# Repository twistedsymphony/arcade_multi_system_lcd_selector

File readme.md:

# twistedsymphony's universal multi-kit LCD Selector (aka CAERTF-MS)

# F.A.Q.

**What is this thing?**

This is a small remote selector that can be adapted and used on DIP-switch based arcade multi-systems. 
Once the device is configured and installed, rather than selecting your game by setting dip switches, users can push the "Up" (D0) and "Down" (D2) buttons to navigate visually through the game list, then push "Select" (D1) to select the game. The selector will then hold the arcade board in reset and electrically configure the dip switches before releasing reset allowing the selected game to boot.

**What is a DIP-switch based arcade multi-system?**

It's pretty niche, but some arcade games share the same electronics and only really have differing software. Arcade Enthusiests have designed and built "multi-systems" that allow switching out the software so that rather than having a whole separate set of electronics for each game, one set of electronics can play multiple games. The simpliest of these multi-systems will often use Dip-switches to set the game, which is cheap and effective but can be quite clumsy and unintuitive to use.

**Why was this made?**

Selecting your game using dip-switches can be frustrating, annoying, and very much non-intuitive. You typically need to have a little chart near by that tells you how to set the dip switches for the game you want to play, and if you want to switch games you have to power everything down to change it. Doing this while your arcade PCB is inside of an arcade cabinet means you sometimes have to be a contortionist with night-vision and the dexterity of a bomb-diffusal expert just to change that game you're playing. A selector like this one, that is easy to use and understand, solves most of those problems. 

This is being made open source in the hopes that future multi-systems that get developed by anyone in the community can easily incorporate support for this benefiting both the functionality of their multi and the users in the community. 

**What features/functinoality does this have?**

You get a full-color TFT display to show the game logos, you get 3 buttons: up, down, and select, so you can scroll through the game list and select the game you'd like to play. Selecting the game displays a loading screen while it resets the PCB and virtually configures the dip switches for game you selected. If an image isn't found it it will display the title of the game as text on the screen, and can seemilessly scroll between text and image based entries. It uses a standard 10-pin IDC ribon cable connection to the multi so you can remote mount the selector outside the cab by simply buying a cable long enough for your setup.

Through the menu configuration file you can control:
* what image is displayed with each game
* what image to display for the loading screen
* what text is to be displayed if an image isn't available
* what the dip configuration is for each selection
* what order you would like the games to appear in (you can even have the same game appear multiple times, in multiple places or with multiple names or images if you like)
* which games you would like displayed in the list or not displayed in the list
* which game you would like to load by default when you first power on
* the amount of idle time before the menu to goes back to displaying the current running game if you scrolled without selecting anything and then stopped

See the section below on "reconfiguring the menu_config.json file" for details on how to adjust these settings.

future features:
* remember last game. The code has support to remember the last selected game on power down and select that game on next power up, but there's a bug that's preventing that from functioning
* Selection over WiFi from your phone or other devie. the selector has Wifi Support so this is possible, the software just needs to be built.

**How Difficult is this to setup and use?**

If you're designing and building a multi kit this will add exactly $0 to your production costs. For the bare minimum support you simply need to add a 10-pin header footprint to your PCB for the selector and a 1-pin header footprint for a reset wire. This adds no cost to production and maybe an hour (not even) of your time to add the header to your schematic and PCB layout. I've even provided pre-configured footprints to allow mounting of the selector directly to your PCB if you have the room for it. If you want stronger support still you can spend a few extra cents per PCB and solder in the headers to each of the footprints you added to make use of the LCD selector completely plug and play for your users.

If you're a user of multis the difficulty varies depending on the multi-kit, setting up the kit at most would require soldering of some simple through-hole parts. The selector itself uses an off-the-shelf display and MCU unit from Adafruit coupled with a custom designed interface PCB that is open source and you can send the design files out and have made completely, or find someone selling them. Installing the software is as simple as copying files over to a USB thumb drive.

**Can this be used on multi-kits that weren't designed for it?**

Potentially, from an electrical standpoint this can be used with any multikit design to select games by up to 7 dip-switches (or jumpers). The challenge is wiring it up in a way that doesn't look like a science-experiment, which will vary greatly depending on the multi. The software is fully customizable, in addition to the "menu" config file there is a separate "multi" config file that allows you to specify the parameters of the multi for the software to tailor itself for it's use without any code changes.

# Putting Together a Selector as a Multi-Kit User

## Building a Selector
To piece together a selector you need 3 parts:
1. An Adafruit ESP32-S2 Reverse TFT Feather, which can be [purchased directly from Adafruit](https://www.adafruit.com/product/5345)
2. An CAERTF-MS Interface PCB, the schematics footprint, BOM, and ready-to-go production files are available within this repo
3. a 10-pin IDC cable. Multi-kits designed for selector mounting using the footprints in this repo are designed to utilize a 1.5in (38mm) length cable which can be [purchased from Adafruit](https://www.adafruit.com/product/556) though any 10-pin (2x5 female to female) IDC cable should work.

the Adafruit ESP32-S2 Reverse TFT Feather unit includes 2 male pin header rows, you will need to solder these to the unit to allow it to plugin to the CAERTF-MS interface PCB. While looking at the LCD with USB port on the left you will want to solder the entire bottom row of pins and the first 4 pins on the top left to allow it to plug into a CAERTF-MS Interface PCB and complete the assembly. 

## Setting up a Software release on a new Selector.
1. With the selector disconnected from both the multi-kit and the CAERTF-MS interface board, and disconnected from any power source, connect a USB-C cable between the selctor and your PC. 
2. If this is the first time configuring the selector the display on the selector should say "Adafruit Feather" with some information about the button and "battery" voltages, this is just the default software loaded. On the back of the display you should see a green and blue LED and there is a small reset button next to the USB port, you'll want to click this button once to reset, then double click it to put it into bootloader mode. If successful you should see the screen change and your PC should recognize a USB storage device called "FTHRS2BOOT" If not, attempt the reset button sequence again (the timing between the first click to reset and the subsequent double click can be tricky to get right)
3. Copy the latest Circuit Python .UF2 file file to the root of the "FTHRS2BOOT" drive. You can [get this file from the circuitpython website]( https://circuitpython.org/board/adafruit_feather_esp32s2_reverse_tft/) (at the time of this writing 9.2.8 was the lastest version and known to work)
4. Once the file has been copied over, the display should automatically restart and it will display some small white text on the screen and you will now see a new USB storage device attached to your computer called "CIRCUITPY"
5. Copy the entire content of a release file over to the root folder of the CIRCUIT PY drive. your computer will likely ask if you want to overwrite code.py, select yes to overwrite.

Releases should include:
  * code.py from the he /source directory here on github 
  * multi_config.json and menu_config.json configuring the selector specificlly to your multi kit
  * a /lib folder with the adafruit_display_text library
  * a /images fold that includes the loading.bmp image along with .bmp images for each game the multi supports.
4. you can now test out the menu to make sure it has the games you expect and see how it functions before connecting it to your multi. If you'd like to ajust settings in "menu_config.json" file you can do so to configure the menu to your liking and confirm those changes work while you still have it hooked up to your PC. it is NOT recommended to adjust the multi_config.json settings as these determine the electrical configurain for the multi.
5. once you're done simply unplug the USB-C cable from the display and now the software on the selector is ready for the multi.

**NOTE: Do not connect the USB-C on the Selector at the same time the 10-pin connector is attached to the Multi PCB** Doing so risks damaging your USB host device. The interface PCB has some protections to help prevent voltage back-feed from the USB port to the Multi-PCB but there are no protections to stop voltage back feed from the multi-PCB to the USB port as such there is risk of damage to your USB Host device.

## Installing a Selector onto your Multi
1. Follow the steps above to build the selector hardware
2. Follow the steps above to install the software on the selector
3. Ensure that all Dips switches on your multi are set to "OFF" (0) and that any rotary selectors are set to position "0". Alternatively, you can completely remove any dips or rotary switches from your multi-PCB (if you set any of these switches to other positions it causes that dip to perminently register as "on" resuling in different selections being made other than the game you selected on the LCD selector)
3. Plug the Adafruit ESP32-S2 Reverse TFT Feather into the CAERTF-MS Interface PCB, Make sure the USB-C port is disconnected (**Do not connect the USB-C on the Selector at the same time the 10-pin connector is attached to the Multi-PCB** the interface PCB has some protections to help prevent voltage back-feed from the USB port to the Multi-PCB but there are no protections to stop voltage back feed from the multi-PCB to the USB port as such there is risk of damage to your USB Host device.)
4. Connect the 10-pin IDC cable between the selector and the appropriate header on your multi-PCB
5. (optional) Install any mounts or brackets that may be avalable for your particular multi

## Making Images for the Selector
Images for the selector should be 240x135 pixels and .bmp format. it's recommended to used 8-bit indexed color format for the .bmp as this should set the file size to 33kb for each image. This is small enough to support 32 images for multis with 5-dip switches (32 game slots) or less. For multis with 6 dips (64 game slots) or 7 dips (128 game slots) you will likely need to get creative with lower bit-depth color or use text rather than images for some games.

While BMP files are larger the processing speed required to decode .jpg or .png compression on images takes about 1-2 seconds per image load which dramatically slows down menu navigation making the game selection experience feel extremely laggy. BMP was chosen as it is essentially uncompressed and is able to load instantly and at 8-bit indexed color is still small enough to support images for all games on nearly all dip-switch based multis.

## reconfiguring the menu_config.json file
The Configuration files on this multi are stored in a json format. You can use any plain text editor (such as notepad) to edit a .json file. If the formatting is incorrect or if any value is set incorrectly the multi will display an error on the screen explaining the issue rather than booting to the menu. It's highly recommeded that you use an existing working menu_config.json file and modify when developing a configuration file for a new multi, or adjusting your preferences for an existing multi. this will help you understand the format and parameters.

"games" are identified with a text string, I use the mame rom name for simplicity and consistency but any string of text can be used so long as it's used consistently through the config file. image file paths are always from the root of the device, and by default will use the "/image/filename.bmp" path and format.

There are three sections to the menu_config.json file, the main configuration which describes how the menu functions, the "game_order" list which simply describe the order that the games will apepar in the menu, and the "gamedefs" list which describes each game, it's title, which image it uses, and it's hex value in dips or on a rotary selector.

The main config has the following value and parameter pairs:
* multi_name: [string] This is simply a string of text to help identify which multi the menu is for, it's not used by the multi at all and really just useful to human readers of the config file.
* default_game: [string] this is the game that will start by default when the multi is powered on, it must be set to a value that matches a game identifier in the gamedefs section. if you do not have a preference it is recommended to set this to which ever game occupies position 0 (all dips off) as that will allow initial board bring up about 2 seconds faster.
* retain_selection: [boolean] this is a true or false value, when true the default_game will be ignored and instead the last game selected when the multi was powered off will be selected by default on next power-on (currently this feature is not functioning)
* idle_timeout: [decimal] this is the number in seconds that when scrolling through the menu without selecting a game that the selector will consider "idle" and return the display to showing the currently loaded game. default value of: 10
* debounce_delay: [decimal] this is number in seconds that subsequent button presses will be ignored. necessary to prevent accidental double taps. default value of: 0.2
* loading_image: [string] the file name and path to the .bmp file that will be used for the loading image when loading a new game. If the file specified does not exist plain text will be displayed instead. default value of: "/images/loading.bmp"
* text_color: [string] the hex value describing the color of the text on the screen when text is displayed instead of an image. default value of "0xFFFFFF"
* left_margin: [integer] the left margin in pixels when text is used on screen instead of an image. default value of: 10
* top_margin: [integer] the top margin in pixels when text is used on screen instead of an image. default value of: 60

The game_order section is simply a json array of all of the game identifiers and the order you wish to see them displayed in the menu. the game identifiers must match those specified in the "gamedefs" section. You may opt to exclude games here if you do not want them to appear on the menu, similarly you can include games in the game order multiple times if you wish for them to appaer multiple times on the menu rotation. The selector offers infinite menu rotation in either direction so the last game appears before the first game and the first game appears after the last game when scrolling.

the gamedefs section is a nested object where gamedefs includes a game object for each game available on the selector. each game object is labeled with a game id. As mentioned above I recommend using mame rom names for the game id for simplicity and consistency, but anything can be used. the only rule is that each game object must have a unique name.

each game object has 3 values:
* title: [string] The display text for the game title to use if an image file is not available. Multiple games can have the same title, though it's not recommended as there would be now way to tell the entries apart when using the menu. This text can be as long as you like, it will auto-resize the text to fit. However long games will be harder to read.
* image: [string] the file name and path to the image file associated with the game. I recommend naming your image files the same as the game id for simplicity and consistency. Multiple games can use the same image, though it's not recommended as there would be no way to tell the entries apart when using the menu. See the section above for details on how to make appropriate images for the selector.
* dip_val: [string] this is the value in hex that identifies which position on a rotary selector, or which dip-switch configuration is associated with the particular game. So for instance for a 4 position dip-switch a value of "1" will be translated to a dip configuraiton of "0001" and a value of "C" will be translated to "1100". Multiple games can use the same dip postion. So you could for instance have a game appear twice with two different names or two different images but use the same dip value.

# Adding Support for this Selector to your Multi as a Multi-Kit Developer
If you're designing and building a multi kit this will add exactly $0 to your production costs. For the bare minimum support you simply need to add a 10-pin header footprint to your PCB for the selector and a 1-pin header footprint for a reset wire. This adds no cost to production and maybe an hour (not even) of your time to add the header to your schematic and PCB layout. I've even provided pre-configured footprints to allow mounting of the selector directly to your PCB if you have the room for it. If you want stronger support still you can spend a few extra cents per PCB and solder in the headers to each of the footprints you added to make use of the LCD selector completely plug and play for your users.

A version of the CAERTF-MS interface board has been created for Apocalypse Multi Kits and released to it's own repo: https://github.com/twistedsymphony/apoc_arcade_multi_system_lcd_selector

## Electrical Pinout for 10-Pin header
The header on both the caertf-ms interface board as well as the header expected on the multi should use a 2.54mm pitch 10-pin male shrouded header with the alinment key in front of pin 5 as shown in the image below.

* *Pin 1* is a Gound pin
* *Pin 2* is a +5V supply from the multi PCB to power the Selector, this is passed through a diode to ensure powe flow only from the multi to the selector and not back feed into the multi from the selector.
* *Pin 3* is the reset signal from the selector to the multi PCB, this should be routed to a header somewhere on the multi so that the user can install a reset wire to the original game PCB. This pin is driven to Ground when attempting to hold reset with Open Drain when not in reset. It is driven by a [Ti SN74LVC1G07DBVR open drain buffer](https://www.ti.com/lit/gpn/sn74lvc1g07)
* *Pins 4-10* are the selector signal pins, these are driven either high (+5v) or low (GND) by a [Ti LC245A buffer chip](https://www.ti.com/lit/ds/symlink/sn74lvc245a.pdf) It is assumed that SEL1 represent the lowest address controlled by the selector additional SEL pins are utilized in order to cover the number of controlled addresses, for instance if your multi has 3 dips then you will use SEL1, SEL2, and SEL3 and leave SEL4-SEL7 disconnected.

## Footprints and mounting considerations
When adding support for this selector on your multi you may opt to use a generic 2.54mm pitch 10-pin male shrouded header footprint on your multi PCB, however special footprints have been developed that can enable mounting of the selector directly to the PCB. There are 8 footprint files in this repo. uniquely identified by "1pos" "2pos" "3pos" and "4pos" to specifies the number of mounting positions that they accomidate. For instance 1pos allows only 1 position for the selector can be mounted while 2pos enables 2 positions offset 90 deg from each other giving your users more mounting options (provided your multi PCB has enough space to accomidate additional mounting options). Each position also has "co" and "nco" variants for "cut-outs" and "no cut-outs". Footprints with cut outs have edge cuts built into the footprints to allow the through-hole pins of the caerft-ms interface pcb to passthrough the multi-pcb so that the PCBs can be mounted directly together with screws without concern of the through-hole solder joints contacting the multi-pcb. the no-cut-outs variants are missing these features and would require either 1.6mm or taller spacers on each screw, or the use of a small 3D printed spacer (included in this repo) to mount the selector to the footprint without the through-hole parts making contact witht he multi-pcb. All footprints are designed to use a IDC cable of 38mm (1.5in) or longer which can be [purchased from Adafruit](https://www.adafruit.com/product/556) though any 10-pin (2x5 female to female) IDC cable should work. An example of a 4-position no cut out footprint with an interface board attached can be seen below.

In addition to directly mounting a selector to the footprint a 3D printed "cradle" has also been created (available in this repo) that can accomodate a selector, this holds the selector at a 45 deg angle for easier viewing and allows the selector to be placed in the cradle for storage or easily removed but the user without any tools. An example of a cradle mount can be seen below.

## Configuring the multi_config.json File
The multi config has the following value and parameter pairs:
* multi_name: [string] This is simply a string of text to help identify which multi the config file is for, it's not used by the multi at all and really just useful to human readers of the config file.
* dip_bits: [integer] This is the number of dip-switch positions that the multi-kit utilizes
* dip_on: [string] Should be set to either "1" or "0", This specifies wether a dip switch being in the "on" position is normal (on = 1, or +5V) or inverted (on = 0, or GND)
* reset_open_drain: [boolean] this should be set to "true" or "false" and determines whether the Adafruit module itself provides and open drain for the rest signal. This should be set to "false" when using the caertf-ms interface pcb as the interface pcb itself has a buffer providing the open drain. it should only be set to true if using the Adafruit unit directly without any interface PCB or if using your own interface PCB that requires this setting adjusted. default vale: false
* dip_bits_reversed: [boolean] This determines the bit order of the dip switches, when "true" SEL1 is the least significant bit, when "false" SEL1 is the most significant bit, with the total bits determined by the "dip_bits" setting above. default vale: false

## Reset wire recommendations
(Additional Details coming soon)

## Example Dip Based Multi-Kit Schematic
(Additional Details coming soon)

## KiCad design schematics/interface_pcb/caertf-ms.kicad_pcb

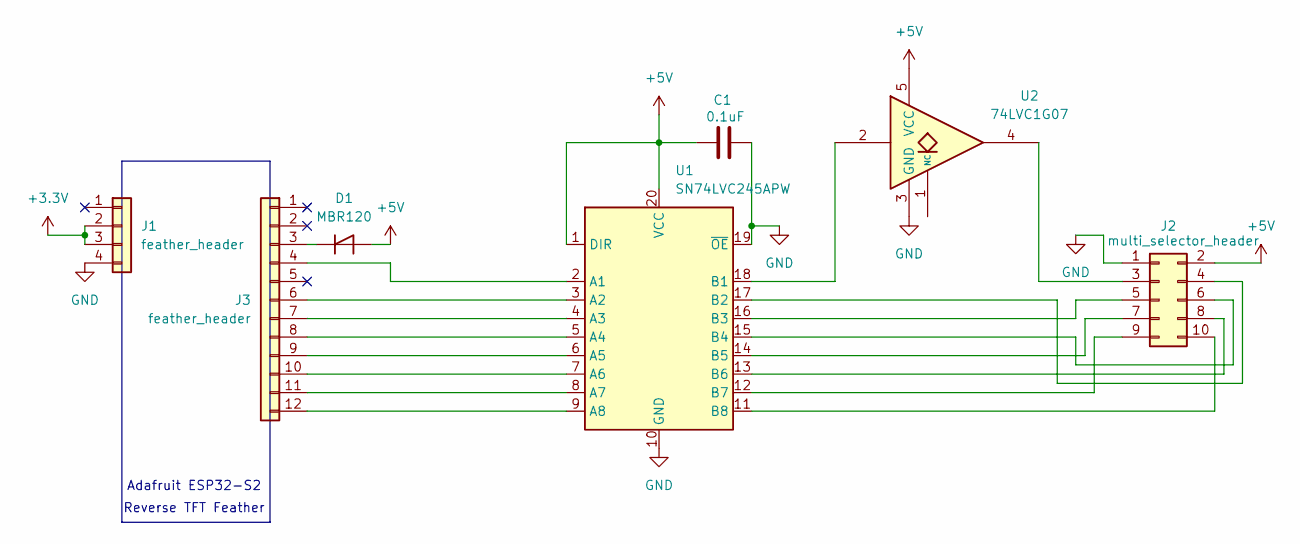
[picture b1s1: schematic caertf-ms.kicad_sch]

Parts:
C1: 0.1uF; C_0805_2012Metric_Pad1.18x1.45mm_HandSolder; JLCPCB Part # C5451689
D1: MBR120; D_SOD-123; JLCPCB Part # C130880
J1: feather_header; PinSocket_1x04_P2.54mm_Vertical; JLCPCB Part # C7509546
J2: multi_selector_header; PinHeader_2x05_P2.54mm_Horizontal; JLCPCB Part # C2682217
J3: feather_header; PinSocket_1x12_P2.54mm_Vertical; JLCPCB Part # C25687189
U1: SN74LVC245APW; TSSOP-20_4.4x6.5mm_P0.65mm; JLCPCB Part # C7848
U2: 74LVC1G07; SOT-23-5; JLCPCB Part # C7829

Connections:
+3.3V: J1.2, J1.3
+5V: C1.1, D1.2 (A), J2.2, U1.1 (DIR), U1.20 (VCC), U2.5 (VCC)
GND: C1.2, J1.4, J2.1, U1.10 (GND), U1.19 (~OE), U2.3 (GND)
unnamed: D1.1 (K), J3.3
unnamed: J2.3, U2.4
unnamed: J2.4, U1.17 (B2)
unnamed: J2.5, U1.16 (B3)
unnamed: J2.6, U1.15 (B4)
unnamed: J2.7, U1.14 (B5)
unnamed: J2.8, U1.13 (B6)
unnamed: J2.9, U1.12 (B7)
unnamed: J2.10, U1.11 (B8)
unnamed: J3.4, U1.2 (A1)
unnamed: J3.6, U1.3 (A2)
unnamed: J3.7, U1.4 (A3)
unnamed: J3.8, U1.5 (A4)
unnamed: J3.9, U1.6 (A5)
unnamed: J3.10, U1.7 (A6)
unnamed: J3.11, U1.8 (A7)
unnamed: J3.12, U1.9 (A8)
unnamed: U1.18 (B1), U2.2

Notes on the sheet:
Adafruit ESP32-S2
Reverse TFT Feather

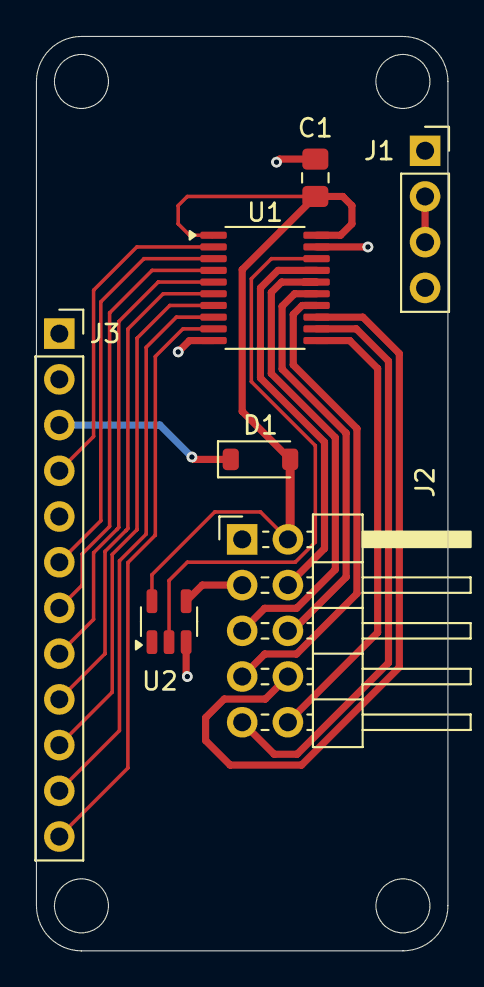
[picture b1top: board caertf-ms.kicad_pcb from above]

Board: 2 copper layers, 22.9 x 50.8 mm, 7 parts (0 on the bottom side), 21 nets.

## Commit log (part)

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2025-06-15 Add files via upload
    Initial Upload
2025-06-15 Update readme.md
    fixed readme.md formatting
2025-06-15 Add files via upload
    Added Footprints and Interface Board Schematics
2025-06-15 Add files via upload
    Added STL printable mount files
2025-06-17 Add files via upload
    added images to support documentation
2025-06-17 Update readme.md
    added info and pictures to the readme
2025-06-17 Update code.py
    Fixed typos in comments
2025-06-22 Updated Footprints
    Updated footprints to improve component outline and Pin 1 identification
2025-07-25 Added Dip reverse order multi config option
    - dip_bits_reversed parameter has been added to multi_config.json allowing the dip bits to be interpreted in reverse order.
2026-04-05 Add files via upload
    Updated config files making use of the some of the updated config feature to sync up with the updated release packages.
